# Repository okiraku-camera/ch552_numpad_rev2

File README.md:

# CH552 Numeric Keypad revision 2

English version is here: [README_en.md](README_en.md)

このリポジトリは、CH552Gマイクロコントローラを使ったシンプルなUSBテンキーを作成するためのハードウェアの作成情報と、このハードウェアを動作させるためのキーボード用ソフトウェアについての情報を含んでいます。

## ハードウェア
**KiCad 6.0**用のファイル一式、製造に用いたガーバーファイル、アクリルカットのための DXF および PDFファイルが、hardware ディレクトリ内に入っています。

## ソフトウェア
上記のハードウェア用に記述した、マクロキーボードにもなるテンキーです。コアパッケージとして **ch55xDuino** (v0.25) を用いた Arduino 用のスケッチです。また、Arduinoのlibrariesディレクトリに `ch552_keyPad_Library` を配置しておく必要があります。

- `macro_numpad/` : マクロテンキーのファームウェアスケッチ
- `html/` : WebHID 設定用 Web UI (macro_numpad.html)

### webhid を使ったマクロキーボードの実装 (macro_numpad)
テンキーの17キーのうち、NumLock を除いた16キーに、**WebHID** を使って好きな UsageID を割り当てられるようにしています。

メディア操作やマウス操作など、ちょっと特別なコードも設定できます。また、1つのキーに複数の UsageID をまとめて登録できるので、ワンアクションで複数のキー入力をまとめて実行することもできます。

WebHIDのサンプル的な意味合いで記述しました。

### マクロキーボードの設定用webアプリケーション (htmlおよびjavascript)
マクロキーボードとWebHIDで通信し、ブラウザに表示する仮想キーボードとデバイス間とでコードの書込みや読出しを行うためのWebアプリケーションです。

## ライセンス
This project contains hardware and software components.

Copyright (c) Takeshi Higasa, okiraku-camera.tokyo

See [LICENSE](./LICENSE)

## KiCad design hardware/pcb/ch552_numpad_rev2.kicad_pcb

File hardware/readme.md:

# ハードウェアについて

CH552Gマイクロコントローラを使ったシンプルなUSBテンキーです。

このプロジェクトには、PCB、FR-4を使ったプレート、アクリル板を使ったポート部品の、KiCad設計ファイルが含まれています。

製造およびアクリルカットに用いたgerber、DXF、およびPDFファイルも含んでいます。

ハードウェアの設計はKiCAD 6.0で行いました。各ディレクトリ内のKiCADプロジェクトファイルを開くことで、回路構成、PCB構成、各プレートの設計内容を見ることができます。

## PCBおよびプレート
PCB、スイッチをはめ込むtop_plate、底板となる bottom_plate は、材質はFR-4で製造時の厚さ指定は1.6mmです。

### PCB
chh552g を使ったふつうのテンキーを作成するためのPCBです。4列5行構成のスイッチマトリックス回路で、17個のMX互換スイッチを使います。スイッチの取付けには Keilh のスイッチソケット (Hotswap socket) を利用します。

PCBの厚さは1.6mm、PCBのネジ穴径は3mmです。このネジ穴にはM2用の真鍮スペーサーが (途中まで) 入ります。

### top_plate
MXスイッチをマウントするためのスイッチプレートです。各スイッチは、13.9mm角の矩形にはめ込みます。MXスイッチの仕様的には14mm角の矩形が求められていますが、実際にスイッチをはめると緩かったりガタつくことがあるので、小さ目にしています。

今回のキーボードはCherryスタイルのプレートマウントスタビライザーを用いるため、そのためのフットプリントを用意しました。

スイッチをはめ込むためのホールは、今回の設計では単純な矩形としていますが、半径0.5mm程度の円弧で丸めた方が割れを防ぐ面で安全です。

プレートの厚さ1.5mm、ネジ穴径は2.4mmです。

### bottom_plate
キーボードの底板になります。1.6mmのPCBを指定し、B面は導体ゾーンと塗りつぶし禁止エリアを組み合わせた市松模様にしました。

ネジ穴径は3mmです。

### 注意点

top_plate\libに含まれている プレートマウントスタビライザー用のフットプリント (MX_Plate_Mount_Stabilizer_2U.kicad_mod) と、M2ネジのマウントホール用フットプリント (MountingHole_M2.kicad_mod) にコートヤードを設定しなかったため、Enterキー用のスタビライザーの一部がネジ穴に干渉します。実装後にスタビライザーの一部を切り取ることで対処可能です。

### アクリルサポート
3枚のプレート (PCB, top, bottom) 間のクリアランスを確保するための、アクリル板によるサポート部材です。アクリル板の厚さや部材(透明、半透明、色など) はアクリルカットをやってくれる業者 (Elecrow社など) に対して指定しています。

### top_support
PCBとtop_plate (スイッチプレート)の間に位置する3mm厚のアクリル板です。

top_supportの上側 (top_plate側) には、1mm厚の隙間テープと呼ばれるウレタンスポンジのテープを貼ることで、ソケットを用いるスイッチに必要な4mm弱のクリアランスを確保しています。

このPCBで使っているUSBレセプタクルの固定用ポストの高さは2.0mmであり、PCBのF面側に若干突き出します。アクリル板との干渉を防ぐため、top_support の該当位置に小さな穴を2つ用意しています。

カットされたアクリル板は、写真のように保護紙が貼られた状態で納品されます。

top_supportのネジ穴にはM2ネジを通しますが、ネジ穴径は工作精度などを考慮して 2.4mmとしています。

### bottom_support
PCBとbottom_plateの間に入る5mm厚のアクリル板を加工したサポート部材です。PCBのB面に実装するUSBコネクタやスイッチソケットと、底板のあいだには約5mmのクリアランスが必要です。

bottom_supportのネジ穴は、M2ネジ用の真鍮スペーサーの外形と同じ3.0mmを指定しています。

## 組み立て
以下の図のように、各プレート、サポートをネジとスペーサーで固定します。

4mm長のM2ネジをねじ込んだ状態のスペーサーを底側から挿入すると、PCBの途中まで達します。その状態でpcbの上に top_supportとtop_plate を置き、上からネジで締め込みます。隙間テープは、top_supportの上側に事前に貼り付けておきます。

bottom_plate, bottom_supportのネジ穴径が3.0mmであるため、組み立て時にはスペーサーを無理やりはめ込むような感触になります。しかしながら、組み立て時に全体を持ち上げてもスペーサーが落下することがないので、作業しやすくなります。

*組み立てに用いるネジとスペーサー*

*仮組みして、スタビライザーがPCBに接触したり、干渉しないことを確認*

*スイッチソケットとbottom_supportが干渉しないことを確認*

*Enterキー位置のネジ穴と干渉するため、スタビライザーをわずかにカット*

*スタビライザーの取り付け動画*

## ファームウェアの更新について
C552の **P3.6ピンを+3.3Vでプルアップした状態で電源を投入**すると、CH552はブートローダーモードで開始し、数秒間その状態を保持します。そのタイミングでファームウェアをUSB経由で送信することで、ファームウェアを更新できます。

このPCBでは P3.6(UDP)のプルアップがしやすいよう基板の上端にBOOTと33Vという2つのスルーホールパッドを用意しています。2つのパッドをピンセットなどで接続した状態で USBケーブルを接続することで、ブートローダーモードが開始します。ファームウェアの転送中もこれらのパッドを接続したままで問題ないようです。

なお、ファームウェアのアップロードが完了しても自動的にリスタートしないため、BOOTの隣にあるリセット用のパッド (RSTと+5V) を接続してハードウェアリセットをかける必要があります。こちらについても、ピンセットでつまんでやる感じです。

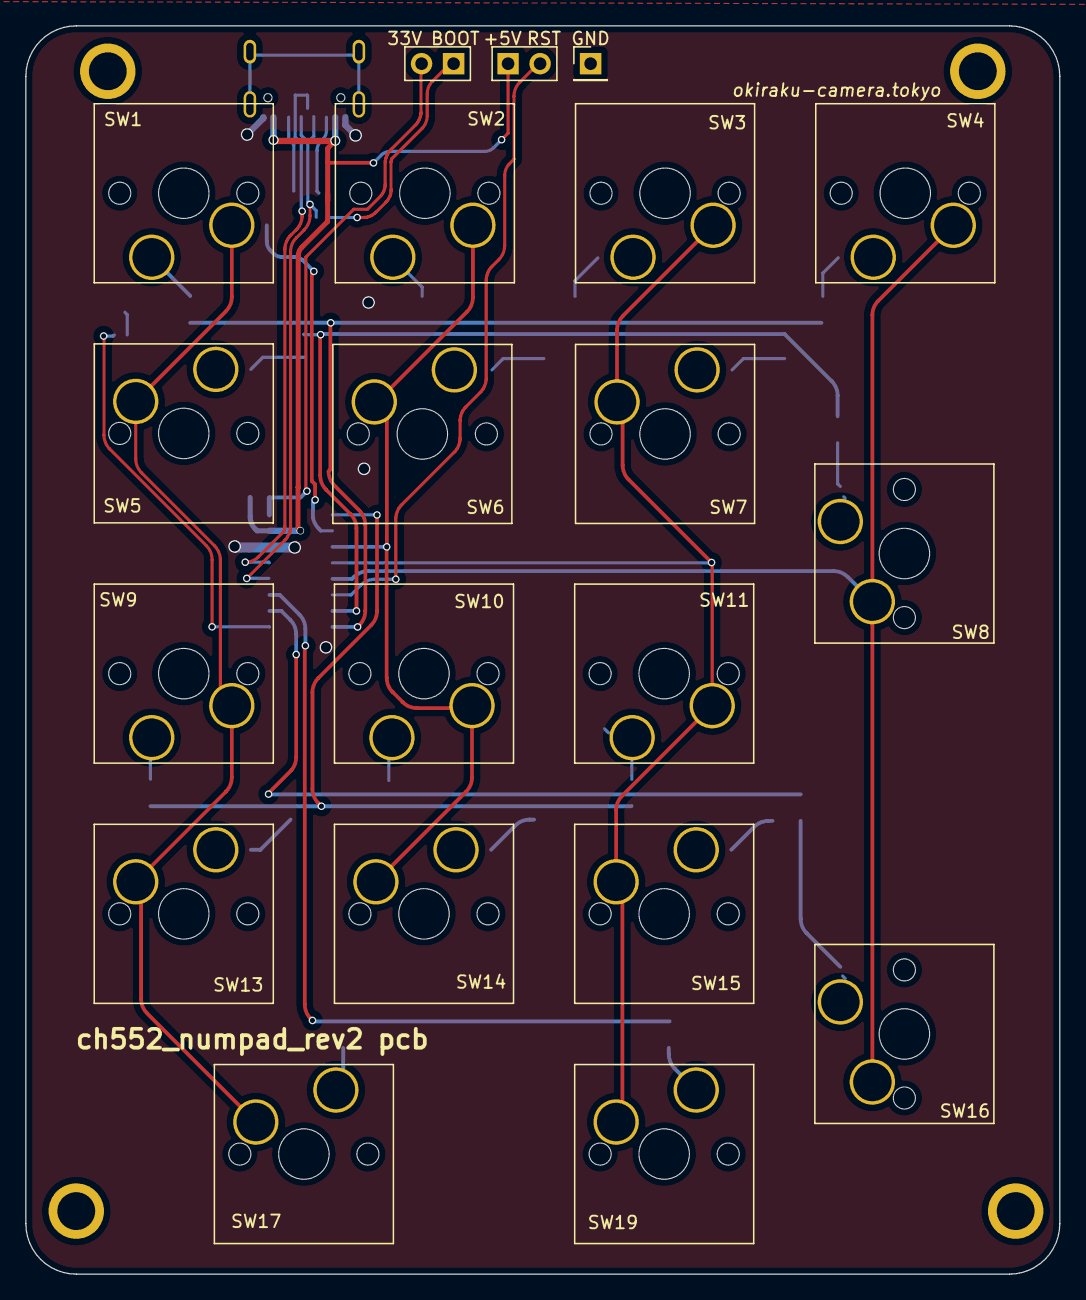
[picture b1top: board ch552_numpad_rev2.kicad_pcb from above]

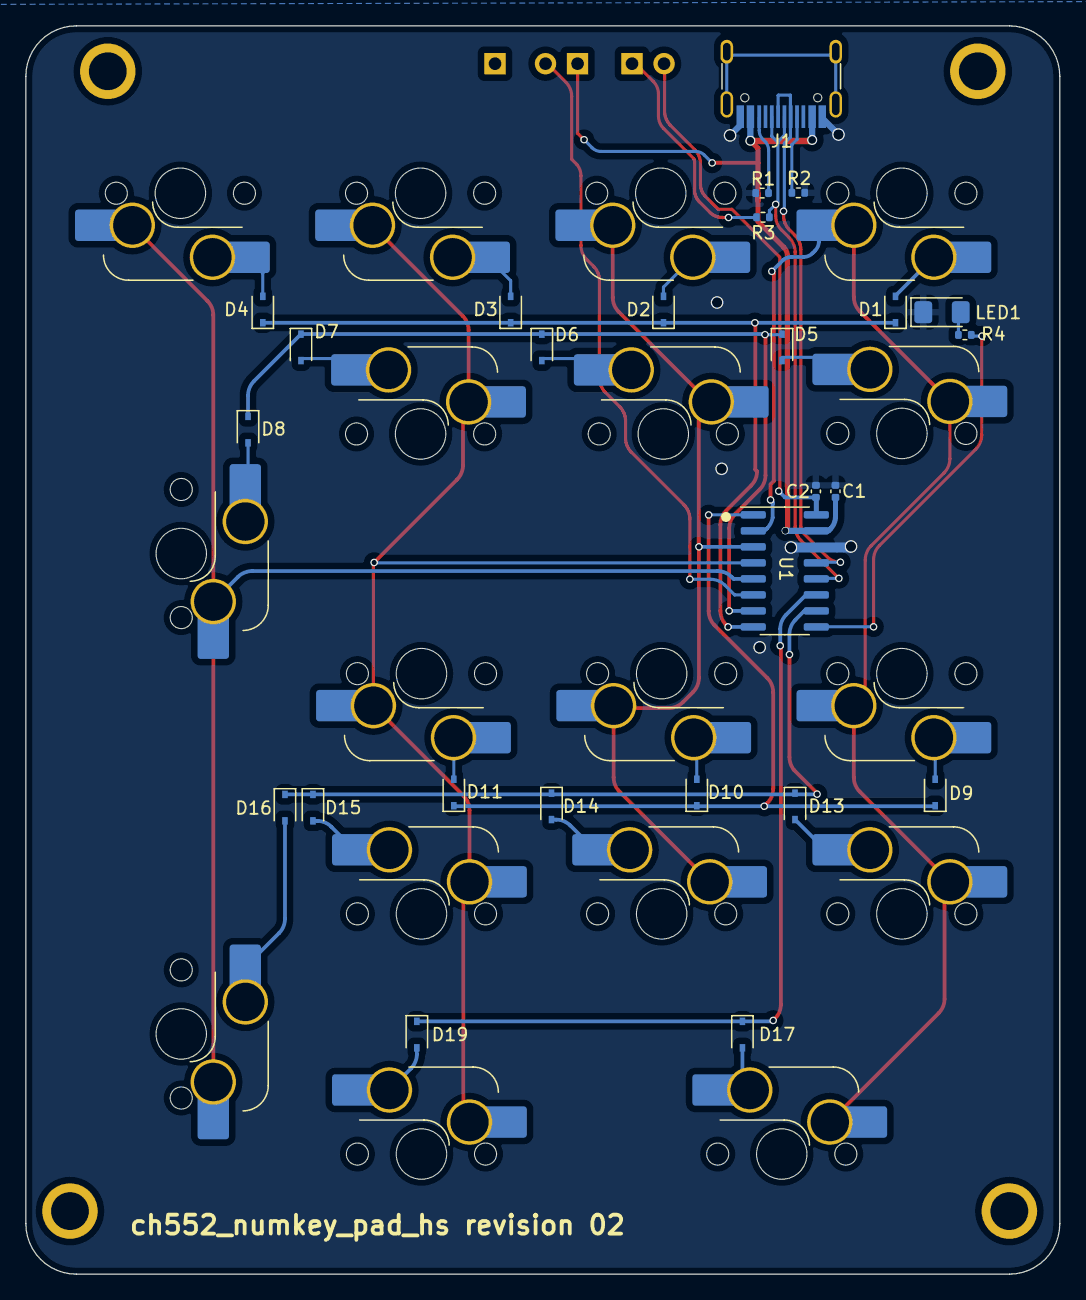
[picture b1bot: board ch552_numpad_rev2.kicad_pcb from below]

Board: 2 copper layers, 82.0 x 99.0 mm, 45 parts (26 on the bottom side), 37 nets.

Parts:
BOOT1: Conn_01x02_Male; PinHeader_1x02_P2.54mm_Vertical
C1, C2: 100nF; C_0402_1005Metric
D1, D2, D3, D4, D5, D6, D7, D8, D9, D10, D11, D13, D14, D15, D16, D17, D19: 1N4148WS; D_SOD-323
J1: USB_C_Receptacle_USB2.0; USB_C_Receptacle_304J-BCP16
LED1: GREEN; LED_1206_3216Metric_Pad1.42x1.75mm_HandSolder
R1, R2: 5.1k; R_0402_1005Metric
R3: 10k; R_0402_1005Metric
R4: 1k; R_0402_1005Metric
RST1: Conn_01x02_Male; PinHeader_1x02_P2.54mm_Vertical
SW1, SW2, SW3, SW4, SW5, SW6, SW7, SW9, SW10, SW11, SW13, SW14, SW15, SW19: SW_Push; SW_Hotswap_Kailh_MX_Plated_1.00u
SW8, SW16, SW17: SW_Push; SW_Hotswap_Kailh_MX_Plated_2.00u
U1: CH552G; SOP-16_3.9x9.9mm_P1.27mm

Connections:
+5V: C1.1, J1.A4 (VBUS), J1.A9 (VBUS), J1.B4 (VBUS), J1.B9 (VBUS), RST1.1, U1.15 (+5V)
/CC1: J1.A5 (CC1), R2.1
/CC2: J1.B5 (CC2), R1.1
/COL1: SW1.1, SW5.1, SW9.1, SW13.1, SW17.1, U1.2 (P1.4/AIN1)
/COL2: SW2.1, SW6.1, SW10.1, SW14.1, U1.3 (P1.5/MOSI/AIN2)
/COL3: SW3.1, SW7.1, SW11.1, SW15.1, SW19.1, U1.4 (P1.6/MISO/RXD1)
/COL4: SW4.1, SW8.1, SW16.1, U1.5 (P1.7/SCK/TXD1)
/NumLED: R4.1, U1.9 (P1.1/AIN0)
/ROW1: D1.1 (K), D2.1 (K), D3.1 (K), D4.1 (K), U1.8 (P3.0/RXD)
/ROW2: D5.1 (K), D6.1 (K), D7.1 (K), D8.1 (K), U1.7 (P3.1/TXD)
/ROW3: D9.1 (K), D10.1 (K), D11.1 (K), U1.1 (P3.2/TXD1)
/ROW4: D13.1 (K), D14.1 (K), D15.1 (K), D16.1 (K), U1.10 (P3.3/INT1)
/ROW5: D17.1 (K), D19.1 (K), U1.11 (P3.4/RXD1)
/RST: RST1.2, U1.6 (RST)
/UDM: J1.A7 (D-), J1.B7 (D-), U1.13 (P3.7/UDM)
/UDP: J1.A6 (D+), J1.B6 (D+), R3.1, U1.12 (P3.6/UDP)
/V33: BOOT1.2, C2.1, U1.16 (V33)
GND: C1.2, C2.2, J1.A1 (GND), J1.A12 (GND), J1.B1 (GND), J1.B12 (GND), LED1.1 (K), R1.2, R2.2, U1.14 (GND)
unnamed: BOOT1.1, R3.2
unnamed: D1.2 (A), SW1.2
unnamed: D2.2 (A), SW2.2
unnamed: D3.2 (A), SW3.2
unnamed: D4.2 (A), SW4.2
unnamed: D5.2 (A), SW5.2
unnamed: D6.2 (A), SW6.2
unnamed: D7.2 (A), SW7.2
unnamed: D8.2 (A), SW8.2
unnamed: D9.2 (A), SW9.2
unnamed: D10.2 (A), SW10.2
unnamed: D11.2 (A), SW11.2
unnamed: D13.2 (A), SW13.2
unnamed: D14.2 (A), SW14.2
unnamed: D15.2 (A), SW15.2
unnamed: D16.2 (A), SW16.2
unnamed: D17.2 (A), SW17.2
unnamed: D19.2 (A), SW19.2
unnamed: LED1.2 (A), R4.2

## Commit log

2026-03-09 readme and license.
2026-03-09 assets
2026-03-09 not md file.
2026-03-09 hardwear first commit.
2026-03-10 Changed some legends
2026-03-10 Add copyrighht message.
2026-03-10 Add simple_Numpad files.
2026-03-14 update documents and images.
2026-03-14 Update Documents.
2026-03-15 Add images and update readme.
2026-03-16 update images and readme
2026-03-28 macro_numpad first commit.
2026-03-28 webhid html first commit
2026-03-31 Cleaning up redundant code
2026-04-06 move files to library
2026-04-06 Add repeat or loop function.
2026-04-06 update docs.
2026-04-06 macro_numpad.ino depends on libbrary.
2026-04-07 html name
2026-05-15 Add document
2026-05-18 update document.
